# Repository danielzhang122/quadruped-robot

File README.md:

# Quadruped Robot

A side project I built for fun over the summer, with a bit of a Watch Dogs vibe. I plan to keep at it once I find the time (and a 3D printer).

A 12-servo, 3D-printable quadruped. It was designed in Fusion 360, exported to URDF, and simulated in MuJoCo. In the sim it stands, trots forward and backward, and turns on the spot. The same controller has a hardware mode for the real servos (PCA9685 board); it's tested against a fake servo board and waits for the first build.

More of my projects: [zhangdz.ca](https://zhangdz.ca)

*In the MuJoCo sim. Click for the full video.*

## To do

- [x] Design the robot in Fusion 360 (v2, with electronics: sized for MG90S servos, a PCA9685 board and a Raspberry Pi Zero 2 W)
- [x] Export the URDF and build the MuJoCo model
- [x] Trot gait controller: stands, walks and turns in the sim
- [ ] Re-export the URDF and sim model from the v2 design
- [x] Custom PCB schematic in KiCad: battery input, fuse and reverse-polarity protection, battery monitor, two 5 V rails, PCA9685, Pi header, 12 servo headers (see [`pcb/`](pcb/README.md))
- [x] PCB layout (99 × 79 mm, 2 layers): fully routed, DRC clean
- [ ] PCB polish: silkscreen tidy-up and labelling so it actually looks nice (labels off pads and inside the edge, + / − on the battery plug, FL / FR / BL / BR by the servo corners, S + − by the servo headers, board name and version, maybe a logo)
- [ ] Order the PCBs (steps in [`pcb/`](pcb/README.md#ordering-when-its-time))
- [ ] 3D-print the parts
- [ ] Assemble: 12 MG90S servos, the custom PCB, Raspberry Pi Zero 2 W, 2S LiPo
- [ ] First power-up: check servo directions (`SERVO_INVERT`) and calibrate
- [ ] Walk on the real robot and tune the gait

### Future (TBD)

- [ ] Computer vision (CV)
- [ ] GUI front end for controlling the robot

## What's here

| Folder | What | Status |
|---|---|---|
| `controller/ik_controller.py` | Trot gait controller (keyboard driven) | Walks in sim. Hardware mode is ready for the first build |
| `mujoco/robot.xml` | MuJoCo model with position actuators | Works |
| `description/` | ROS 2 package `quadruped_description`: URDF (`urdf/quadruped.urdf.xacro`) + STL meshes, originally exported by [fusion2urdf-ros2](https://github.com/dheena2k2/fusion2urdf-ros2) | Source of the model |
| `cad/` | Fusion 360 designs, see below | Open in Fusion 360 |
| `experimental/` | RL training, URDF-to-MuJoCo conversion scripts, pose tools, Isaac Sim USD files | **Didn't work / untested**, see [its README](experimental/README.md) |
| `pcb/` | Custom PCB (KiCad 10, `quadped.kicad_pro`): 2S LiPo input with fuse and reverse-polarity protection, INA219 battery monitor, separate 5 V rails for servos and Pi, PCA9685 servo driver, Pi Zero header, 12 servo headers | Design complete: schematic and layout done, fully routed. Not ordered yet. See [its README](pcb/README.md) |
| `tests/` | Gait unit tests, hardware mapping tests (fake servo board), headless sim tests (stands, walks, turns) | Pass |
| `media/` | Sim video (`quadruped-sim.mp4`) and the GIF shown above | |

### CAD files

| File | What |
|---|---|
| `cad/quadruped-v2-may-2026.f3z` | **Latest design** (May 2026), with the electronics added. `.f3z` is a Fusion archive that bundles all linked parts. In Fusion 360: File → Open → Open from my computer |
| `cad/quadruped-v1-urdf-source.f3d` | Earlier version that the URDF, meshes and MuJoCo model were exported from |

The sim still uses the v1 geometry. Re-export the URDF from v2 to bring it up to date.

### Part names

Meshes, URDF links and MuJoCo bodies all use `<leg>_<segment>`: leg is `fr`, `br`, `fl`, `bl` (front/back, right/left) and segment is `hip`, `mid`, `end` (`end` is the foot). The body is `base_link` + `base_upper`. Joints and servos are named `frontRightHip`, `frontRightMid`, ... `backLeftEnd`.

## Setup

Use Python 3.10 or newer, and set up a virtual environment (a self-contained Python install for this project):

```
python -m venv .venv
.venv\Scripts\activate          # Windows   (Linux / Pi: source .venv/bin/activate)
pip install -r requirements.txt
```

## Run

```
python controller/ik_controller.py            # MuJoCo sim with keyboard control
python controller/ik_controller.py --vx 0.5   # walk forward at half stride without touching the keyboard
python controller/ik_controller.py --hardware # real robot (Raspberry Pi + PCA9685)
```

| Key | Action |
|---|---|
| Arrow up / down | Walk forward / backward |
| Arrow left / right | Turn left / right |
| Shift / Space | Raise / lower the body |
| R (hold) | Ease the height back to normal |
| X | E-stop: freeze in place |
| C | Clear e-stop |
| Esc | Return to rest pose and quit |

The keyboard is read with `pynput`, which listens to the whole system. Keys still work when the viewer window isn't focused.

## How the controller works

It's an open-loop **joint-space** trot, not inverse kinematics. The diagonal leg pairs (FR+BL and FL+BR) swing half a cycle apart. On each step:
- the hip sweeps forward and back,
- the mid joint lifts the foot during the swing,
- the end joint tucks the foot.

Speed and turning are fractions of a full stride, from -1 to 1.

- All angles are in the URDF/MuJoCo joint frame, and joint limits are read from `mujoco/robot.xml`, so the sim and the servo mapping can't disagree.
- The gait settings are grouped at the top of the file (`GAIT_FREQ`, `SWING_HIP`, `STEP_HEIGHT`, ...). The current values were tuned in the sim: about 0.11 m/s walking and about 30°/s turning, with no tip-overs in the test scenarios.
- **First power-up on hardware:** check each servo's direction and flip it in `SERVO_INVERT` if needed. Each joint's range is mapped linearly onto the servo's 0–180°.
- On hardware, a servo is only re-sent when its angle changes by at least `SERVO_DEADBAND` (0.1°). Every servo write is a separate I2C message to the PCA9685, so this saves the most time. When the robot stands still, nothing is sent at all.

### Changes from the earlier version
- **Coordinate frame bug fixed.** The old `REST_POSE` and `JOINT_LIMITS` were in a different frame from `robot.xml`, so MuJoCo clamped many commands. The robot crouched at about 0.065 m and drifted 20° over 10 s of walking. It now stands on its feet at about 0.14 m and walks straight. The old version did turn slightly faster.
- The `--sim` flag was ignored, so the script always ran the sim. Sim is now the default, and `--hardware` selects the real robot.
- Paths are resolved relative to the script, so it can be run from any folder.
- If `pynput` is missing, the robot now stands still (it used to start walking on its own). If the servo board isn't found, the script stops with an error instead of running blind. On hardware, the servos go limp at shutdown.
- The loop runs at a fixed rate without drifting, and shutdown no longer renders after the viewer is closed.
- The control logic (`Controller.step`) is separate from the sim and hardware I/O, so it's testable.
- Optimized:
  - Unchanged servos are skipped on hardware (see above).
  - The gait computes one sin/cos per tick instead of four.
  - The sim writes all 12 actuators in one call.
  
  The output is identical to before. One control step takes about 3 µs of the 10 ms budget.
- Renamed everything from the Fusion export names (`forurdf2`, `FRend_1`, `backrighthip_1`, ...) to the scheme above. The ROS launch file pointed at a `forurdf2.xacro` that didn't exist. It now points to `quadruped.urdf.xacro`.

## Tests

```
pip install pytest
pytest
```

The sim tests run MuJoCo without a window. They check that only the feet touch the ground, and that the robot walks forward and backward and turns the right way without tipping over.

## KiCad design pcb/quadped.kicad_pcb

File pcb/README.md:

# Quadruped PCB

My first PCB: a 99 × 79 mm carrier board that sits on top of the robot and ties everything together. A 2S LiPo plugs in, the Raspberry Pi Zero 2 W plugs on top, and all 12 servos plug in at the corners.

**Status:** designed in KiCad 10, fully routed and DRC clean. Not ordered yet. Next up is the silkscreen and labelling pass to make it look as good as it works.

Open `quadped.kicad_pro` in KiCad 10 or newer.

---

## What it does

1. **Takes battery power safely:** fuse, reverse-polarity protection and a battery monitor.
2. **Makes two separate 5 V supplies:** one for the servos, one for the Pi, so servo current spikes can't reset the Pi.
3. **Connects the Pi to the servos:** the Pi talks I2C to a PCA9685, which drives the 12 servo signals.

The controller code doesn't change: the PCA9685 is at I2C address `0x40`, same as the Adafruit breakout `ServoKit` already expects.

```
                         ┌──► U2 buck 5 V / 5 A ───► +5V_SERVO ──► 12 servos
 2S LiPo ─► J1 ─► F1 ─► Q1 ─► R2 shunt ─┤
 7.4 V      XT30  7.5 A  reverse  │      └──► U3 buck 5 V / 2.5 A ─► +5V_PI ──► Pi Zero 2 W
                         polarity │                                            │ 3.3 V
                                  U1 INA219 ◄──────── I2C ─────────────────────┤
                                  (0x41)              U4 PCA9685 (0x40) ◄──────┤
                                                      └─► 12 servo signals     │
                                                      J3 Qwiic port ◄──────────┘
```

---

## The circuit

### 1. Battery input

| Part | Does |
|---|---|
| **J1** XT30 | Battery plug. Pin 2 is +. |
| **F1** 7.5 A mini blade fuse | Blows on a short instead of the LiPo. Walking draws 2–4 A, so it won't trip in normal use. |
| **Q1** AOD4185 P-MOSFET | Reverse-polarity protection. Battery the right way: fully on, almost no loss. Backwards: off, nothing gets power. Wastes far less than a diode would at 5 A. |
| **R1** 10 kΩ | Pulls Q1's gate to ground, which is what turns it on. |

Output: `VBAT` (6.6–8.4 V).

### 2. Battery monitor

| Part | Does |
|---|---|
| **R2** 0.01 Ω shunt | All battery current flows through it. At 5 A it drops just 0.05 V. |
| **U1** INA219 | Reads the voltage across R2 (current) and the battery voltage, and reports both over I2C. Lets the Pi stop before the LiPo drains below a safe level. |
| **C1** 100 nF | Decoupling for U1. |

**I2C address:** the INA219 has 16 built-in addresses (0x40–0x4F), picked by how its A0 and A1 pins are wired. Both on GND would give 0x40 and clash with the PCA9685, so A0 goes to 3.3 V for **0x41**.

Output: `VBAT_SENSE`, which feeds both regulators.

### 3. Power rails

| Part | Does |
|---|---|
| **U2** 5 V / 5 A buck module | Servo supply (`+5V_SERVO`). |
| **U3** 5 V / 2.5 A buck module | Pi supply (`+5V_PI`). Separate so servo noise can't reach the Pi. |
| **C2** 100 µF | Input reserve next to both bucks. |
| **C3, C4** 1000 µF | Servo reserve, one by the front servos and one by the back. They supply current bursts faster than the buck can react. |
| **D1, D2** + **R3, R4** | Power LEDs for each rail. |

Bucks are ready-made modules (e.g. Pololu D24V50F5 / D24V22F5) on header pins, so no switching-regulator layout to get wrong. The footprints are 3-pin placeholders until the exact modules are picked.

### 4. Pi, servo driver and servos

| Part | Does |
|---|---|
| **J2** 2×20 header | The Pi plugs in here. 5 V in on pins 2/4, 3.3 V out on pin 1, I2C on pins 3/5, servo enable on pin 11 (GPIO17). |
| **U4** PCA9685 | Turns I2C commands into 16 PWM outputs (12 used). Runs on 3.3 V to match the Pi. Address 0x40. |
| **C5, C6** | Decoupling for U4. |
| **R5** 10 kΩ + **JP1** | R5 holds U4's output-enable off at boot so the servos don't twitch before the code runs; GPIO17 turns them on. Bridge JP1 to skip that and keep outputs always on. |
| **R6–R17** 220 Ω | One per servo signal. Protects U4 if a servo wire shorts. |
| **J15–J26** | Servo plugs, three per corner. Signal / 5 V / GND, GND toward the board edge. |
| **J3** Qwiic | Spare I2C port for an IMU later. |
| **R18, R19** | Spare I2C pull-up pads, not fitted (the Pi has its own). |
| **TP1–TP5** | Test points: VBAT, 5 V servo, 5 V Pi, 3.3 V, GND. |

**Servo channels** match `SERVO_CHANNELS` in the controller:

| Leg | Headers | Channels |
|---|---|---|
| FR | J15–J17 | 0–2 |
| BR | J18–J20 | 3–5 |
| FL | J21–J23 | 6–8 |
| BL | J24–J26 | 9–11 |

Each leg's three headers are hip, mid, end, in that order.

---

## The board

- **99 × 79 mm, 2 layers.** Mounted on top of the robot with the battery underneath. Front is along the 99 mm length.
- **Layout:** power runs up the left in battery order. The Pi sits lengthwise on the right with its camera end forward. Servo headers sit at the four corners, nearest their legs. Only flat parts go under the Pi.
- **Tracks:** power nets are 1.5 mm, signals 0.15–0.2 mm. Ground is a copper fill on both layers, stitched together with vias.
- **Mounting:** 4× M3 at the corners, 4× M2.5 for the Pi.

```
                 FRONT
   ┌──────────── 79 mm ────────────┐
   │ [FL servos]       [FR servos] │
   │       C3                      │
   │                ┌── camera ──┐ │
   │  U2  U3        │            │ │
   │                │  Pi Zero   │ │ 99 mm
   │  R2  U1        │  (U4 and   │ │
   │                │  R6–R17    │ │
   │  Q1            │  under it) │ │
   │  F1            └──── SD ────┘ │
   │        J1 XT30   C4           │
   │ [BL servos]       [BR servos] │
   └───────────────────────────────┘
                 BACK
```

### Worth knowing

- **J2 uses a `PinHeader_2x20` footprint**, with a female socket soldered into it. KiCad's `PinSocket` footprints are mirrored for boards that face each other, which would swap the Pi's 5 V and GND pins here.
- **The XT30 opening faces the board edge**, with the pins on the inside.
- **DRC exclusions:** servo header courtyards overlap because they sit side by side at 2.54 mm on purpose.

---

## Ordering (when it's time)

1. File → Fabrication Outputs → **Gerbers** (F/B.Cu, F/B.Silkscreen, F/B.Mask, Edge.Cuts) and **Drill Files** into one folder. Zip it.
2. Upload to JLCPCB or PCBWay: 2 layers, 1.6 mm, 1 oz copper, HASL lead-free.
3. Optional: have the factory assemble U1 and U4 (fine-pitch chips) using the BOM and position files.
4. Buy separately: XT30 male (PW), Keystone 3568 fuse holder + 7.5 A fuse, 2×20 female socket, 12× 1×3 headers, the three electrolytic caps, both buck modules.

**First power-up:** check for shorts with a multimeter first. Then power it from a current-limited bench supply with no Pi and no servos, and check both rails read about 5 V. Then add the Pi (`i2cdetect -y 1` should show 40, 41 and 70), then one servo, then all 12.

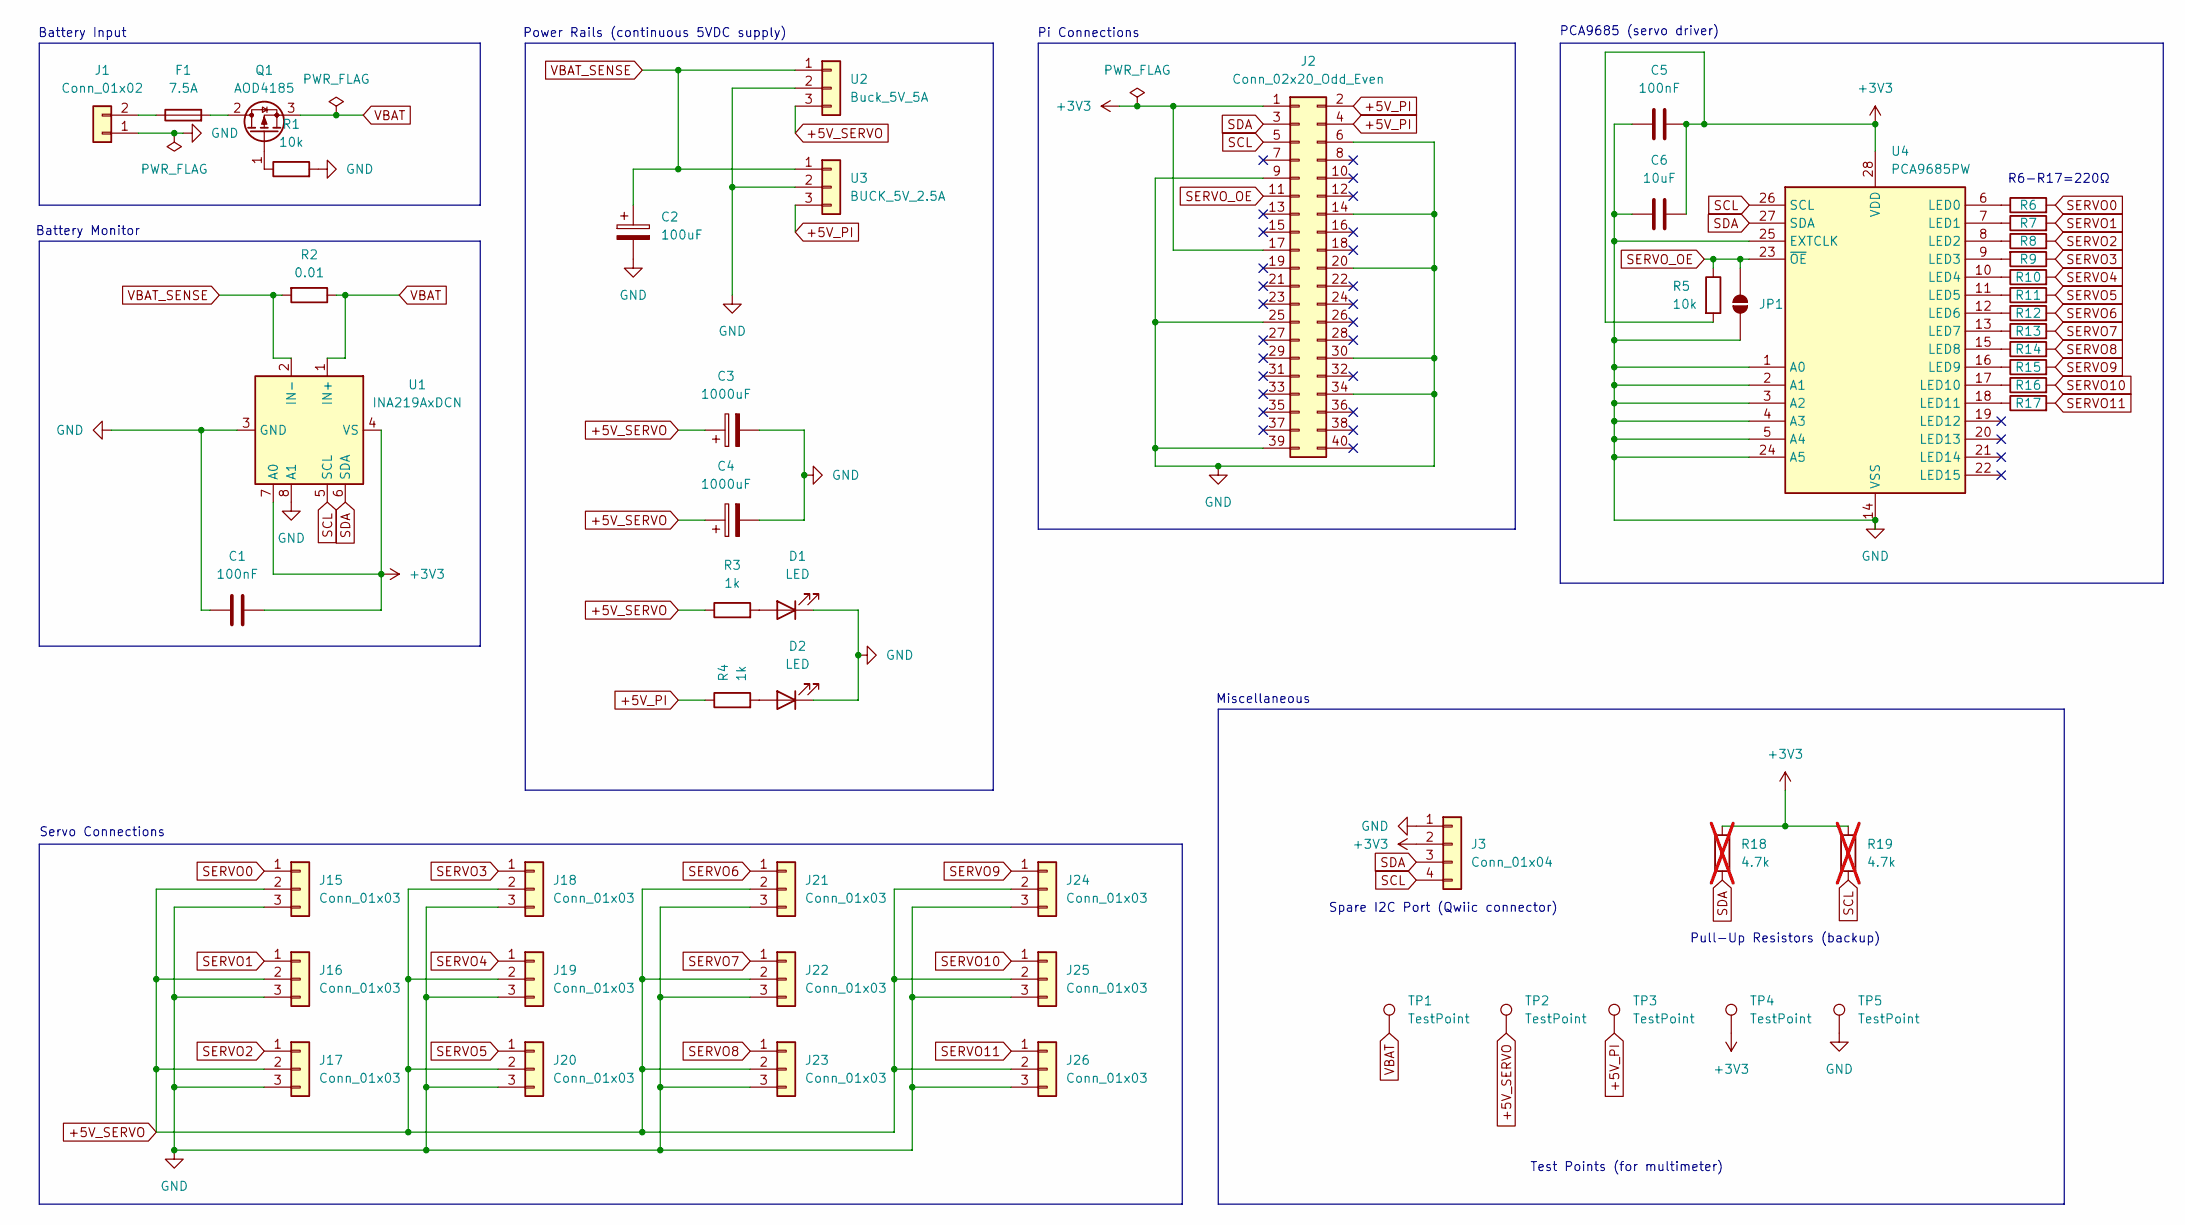
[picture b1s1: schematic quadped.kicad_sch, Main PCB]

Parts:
C1, C5: 100nF; C_0805_2012Metric
C2: 100uF; CP_Radial_D6.3mm_P2.50mm
C3, C4: 1000uF; CP_Radial_D10.0mm_P5.00mm
C6: 10uF; C_0805_2012Metric
D1, D2: LED; LED_0805_2012Metric
F1: 7.5A; Fuseholder_Blade_Mini_Keystone_3568
J1: Conn_01x02; AMASS_XT30PW-M_1x02_P2.50mm_Horizontal
J2: Conn_02x20_Odd_Even; PinHeader_2x20_P2.54mm_Vertical
J3: Conn_01x04; JST_SH_SM04B-SRSS-TB_1x04-1MP_P1.00mm_Horizontal
J15, J16, J17, J18, J19, J20, J21, J22, J23, J24, J25, J26: Conn_01x03; PinHeader_1x03_P2.54mm_Vertical
JP1: BYPASS; SolderJumper-2_P1.3mm_Open_Pad1.0x1.5mm
Q1: AOD4185; TO-252-2
R1, R5: 10k; R_0805_2012Metric
R2: 0.01; R_2512_6332Metric
R3, R4: 1k; R_0805_2012Metric
R6, R7, R8, R9, R10, R11, R12, R13, R14, R15, R16, R17: 220; R_0805_2012Metric
R18, R19: 4.7k; R_0805_2012Metric; not fitted
TP1, TP2, TP3, TP4, TP5: TestPoint; TestPoint_Pad_D1.5mm
U1: INA219AxDCN; SOT-23-8
U2: Buck_5V_5A; PinHeader_1x03_P2.54mm_Vertical
U3: BUCK_5V_2.5A; PinHeader_1x03_P2.54mm_Vertical
U4: PCA9685PW; TSSOP-28_4.4x9.7mm_P0.65mm

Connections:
+3V3: C1.2, C5.2, C6.2, J2.1, J2.17, J3.2, R5.2, R18.2, R19.1, TP4.1 (1_1), U1.4 (VS), U1.7 (A0), U4.28 (VDD)
+5V_PI: J2.2, J2.4, R4.1, TP3.1 (1_1), U3.3
+5V_SERVO: C3.1, C4.1, J15.2, J16.2, J17.2, J18.2, J19.2, J20.2, J21.2, J22.2, J23.2, J24.2, J25.2, J26.2, R3.1, TP2.1 (1_1), U2.3
GND: C1.1, C2.2, C3.2, C4.2, C5.1, C6.1, D1.1 (K), D2.1 (K), J1.1, J2.6, J2.9, J2.14, J2.20, J2.25, J2.30, J2.34, J2.39, J3.1, J15.3, J16.3, J17.3, J18.3, J19.3, J20.3, J21.3, J22.3, J23.3, J24.3, J25.3, J26.3, JP1.1 (A), R1.2, TP5.1 (1_1), U1.3 (GND), U1.8 (A1), U2.2, U3.2, U4.1 (A0), U4.2 (A1), U4.3 (A2), U4.4 (A3), U4.5 (A4), U4.14 (VSS), U4.24 (A5), U4.25 (EXTCLK)
unnamed: D1.2 (A), R3.2
unnamed: D2.2 (A), R4.2
unnamed: F1.1, J1.2
unnamed: F1.2, Q1.2 (D)
unnamed: Q1.1 (G), R1.1
unnamed: R6.1, U4.6 (LED0)
unnamed: R7.1, U4.7 (LED1)
unnamed: R8.1, U4.8 (LED2)
unnamed: R9.2, U4.9 (LED3)
unnamed: R10.1, U4.10 (LED4)
unnamed: R11.1, U4.11 (LED5)
unnamed: R12.1, U4.12 (LED6)
unnamed: R13.1, U4.13 (LED7)
unnamed: R14.1, U4.15 (LED8)
unnamed: R15.1, U4.16 (LED9)
unnamed: R16.1, U4.17 (LED10)
unnamed: R17.1, U4.18 (LED11)
SCL: J2.5, J3.4, R19.2, U1.5 (SCL), U4.26 (SCL)
SDA: J2.3, J3.3, R18.1, U1.6 (SDA), U4.27 (SDA)
SERVO0: J15.1, R6.2
SERVO1: J16.1, R7.2
SERVO2: J17.1, R8.2
SERVO3: J18.1, R9.1
SERVO4: J19.1, R10.2
SERVO5: J20.1, R11.2
SERVO6: J21.1, R12.2
SERVO7: J22.1, R13.2
SERVO8: J23.1, R14.2
SERVO9: J24.1, R15.2
SERVO10: J25.1, R16.2
SERVO11: J26.1, R17.2
SERVO_OE: J2.11, JP1.2 (B), R5.1, U4.23 (~OE)
VBAT: Q1.3 (S), R2.1, TP1.1 (1_1), U1.1 (IN+)
VBAT_SENSE: C2.1, R2.2, U1.2 (IN-), U2.1, U3.1

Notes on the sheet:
PCA9685 (servo driver)
Pi Connections
Battery Input
Test Points (for multimeter)
Spare I2C Port (Qwiic connector)
Power Rails (continuous 5VDC supply)
R6-R17=220Ω
Battery Monitor
Miscellaneous
Pull-Up Resistors (backup)
Servo Connections

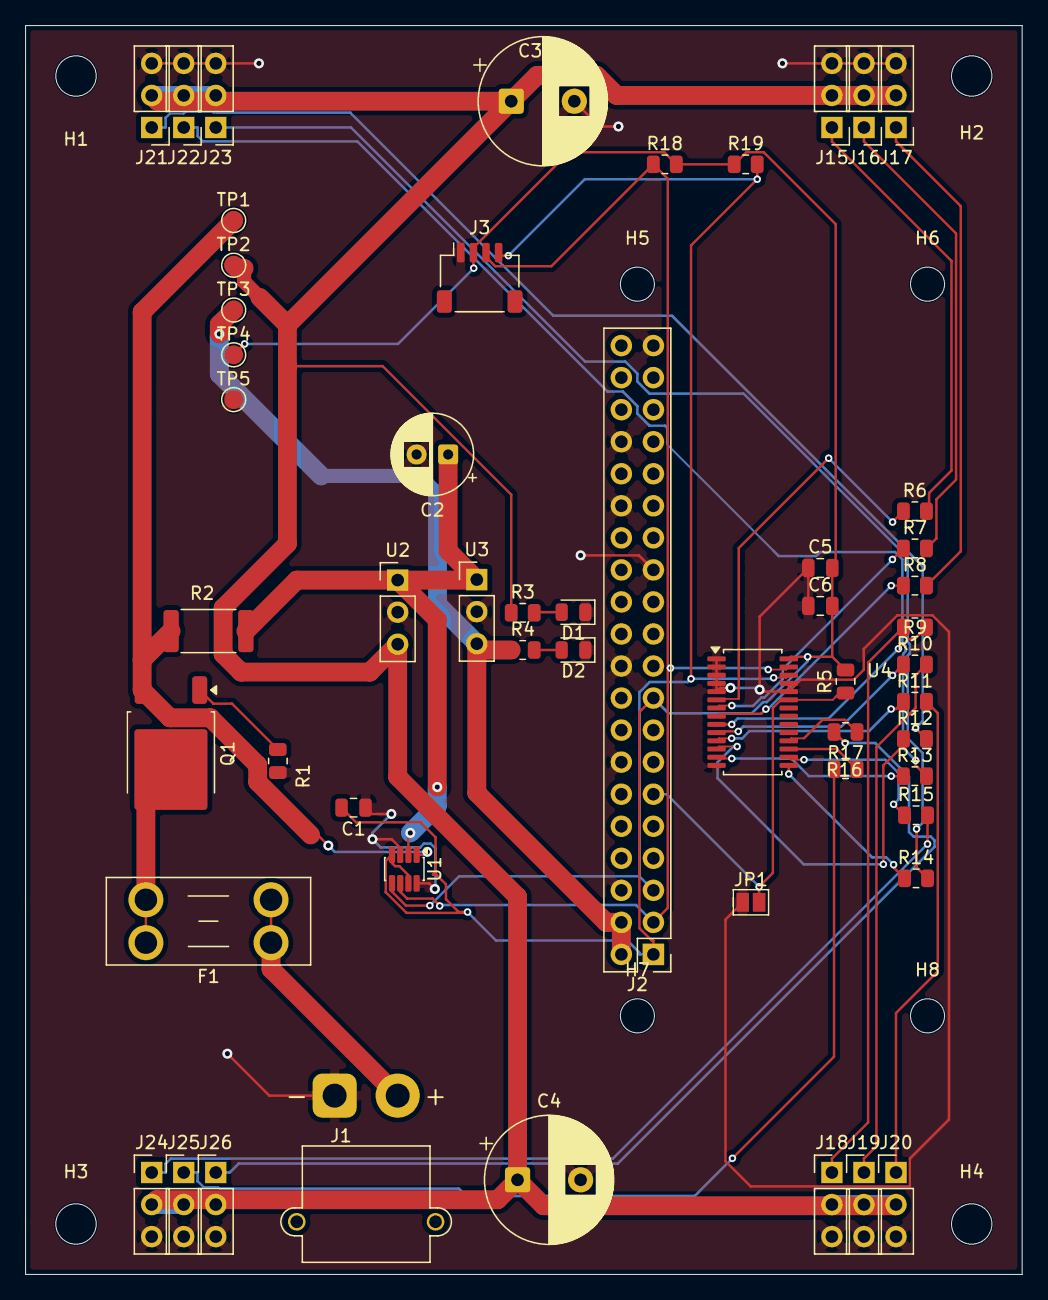
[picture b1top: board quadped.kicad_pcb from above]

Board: 2 copper layers, 79.0 x 99.0 mm, 62 parts (0 on the bottom side), 38 nets.

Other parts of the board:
H1, H2, H3, H4: MountingHole_3.2mm_M3
H5, H6, H7, H8: MountingHole_2.7mm_M2.5
